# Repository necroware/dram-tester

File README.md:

# 4164 / 41256 DRAM Tester

This is a simple DRAM tester for 4164 and 41256 DRAM chips. It writes and reads
various patterns to verify the integrity of the memory chips. During the the
test red an green LEDs blink alternatively to indicate that the test is running.
If an error was detected, the the red LED will stay on permanently. If the chip
passed the test, the green LED will stay on. With JP1 closed, the tester will
expect a 4164 chip, with JP1 open, it will expect a 41256 chip.

## Why do we need this?

When working with vintage computers, it's common to encounter faulty DRAM chips.
This tester helps to quikly identify bad chips. There is no particular reason
why I decided to make this tester. There are already many similar designs, but
the ones I found were either too slow, or didn't work for me. So I decided to
learn a bit more about DRAMs and make my own tester which is fast and simple.

## Bill of Materials
- Arduino Nano or compatible board
- DIP-16 ZIF socket for 4164/41256 DRAM chips
- 2x 330 Ohm resistors (for LEDs)
- 2x LEDs (red and green)
- 22-100µF capacitor (for power supply stabilization)
- 2x1 2.54mm jumper (for JP1)

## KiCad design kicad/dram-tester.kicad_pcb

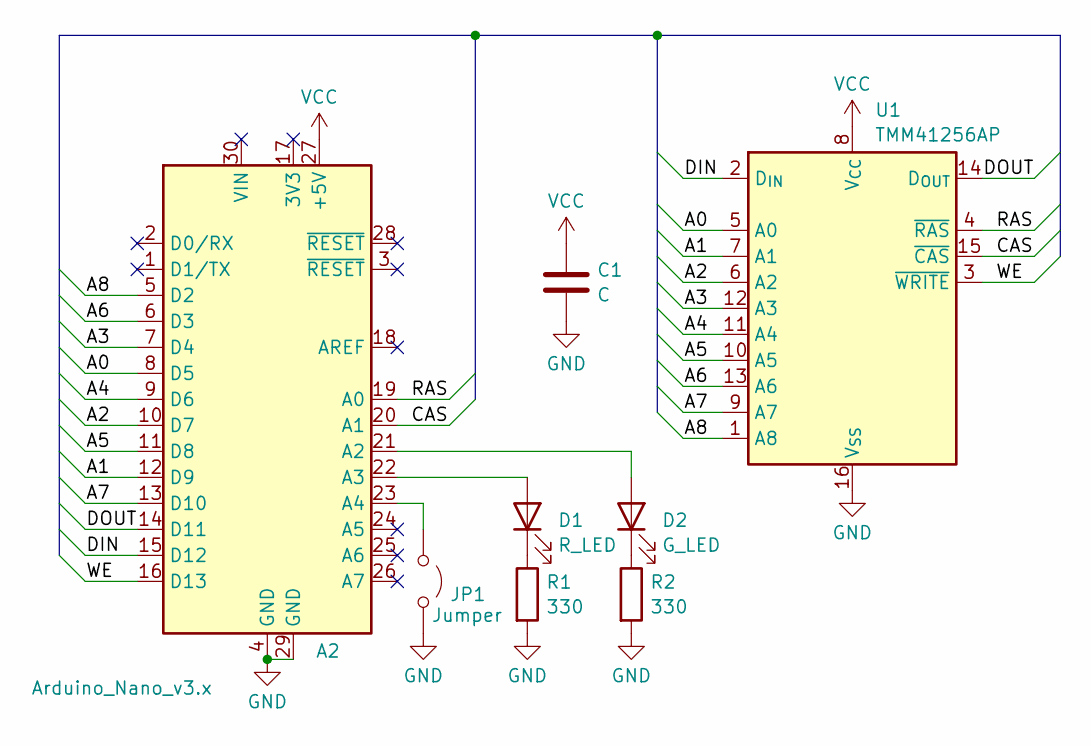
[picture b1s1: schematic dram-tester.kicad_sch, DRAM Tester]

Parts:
A2: Arduino_Nano_v3.x; Arduino_Nano
C1: C; C_Disc_D3.4mm_W2.1mm_P2.50mm
D1: R_LED; LED_D3.0mm
D2: G_LED; LED_D3.0mm
JP1: Jumper; PinHeader_1x02_P2.54mm_Vertical
R1, R2: 330; R_Axial_DIN0207_L6.3mm_D2.5mm_P10.16mm_Horizontal
U1: TMM41256AP; DIP_Socket-16_W4.3mm_W5.08mm_W7.62mm_W10.16mm_W10.9mm_3M_21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

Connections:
/A0: A2.8 (D5), U1.5 (A0)
/A1: A2.12 (D9), U1.7 (A1)
/A2: A2.10 (D7), U1.6 (A2)
/A3: A2.7 (D4), U1.12 (A3)
/A4: A2.9 (D6), U1.11 (A4)
/A5: A2.11 (D8), U1.10 (A5)
/A6: A2.6 (D3), U1.13 (A6)
/A7: A2.13 (D10), U1.9 (A7)
/A8: A2.5 (D2), U1.1 (A8)
/CAS: A2.20 (A1), U1.15 (~CAS)
/DIN: A2.15 (D12), U1.2 (D_{IN})
/DOUT: A2.14 (D11), U1.14 (D_{OUT})
/RAS: A2.19 (A0), U1.4 (~RAS)
/WE: A2.16 (D13), U1.3 (~WRITE)
GND: A2.4 (GND), A2.29 (GND), C1.2, JP1.2 (B), R1.2, R2.2, U1.16 (V_{SS})
unnamed: A2.21 (A2), D2.2 (A)
unnamed: A2.22 (A3), D1.2 (A)
unnamed: A2.23 (A4), JP1.1 (A)
unnamed: D1.1 (K), R1.1
unnamed: D2.1 (K), R2.1
VCC: A2.27 (+5V), C1.1, U1.8 (V_{CC})

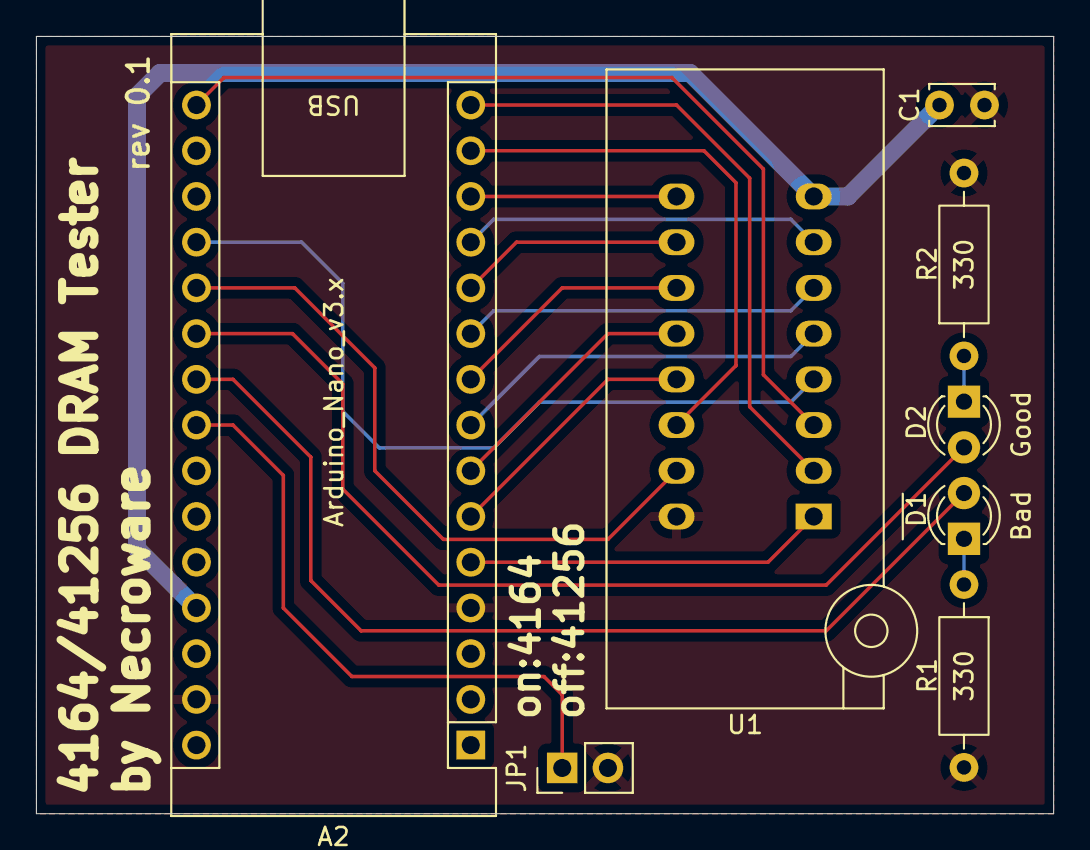
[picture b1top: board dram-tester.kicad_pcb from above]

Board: 2 copper layers, 56.5 x 43.2 mm, 8 parts (0 on the bottom side), 21 nets.

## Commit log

2026-01-06 Add license
2026-01-16 minor fixes
2026-01-16 add logos
2026-01-16 fix A8 trace
